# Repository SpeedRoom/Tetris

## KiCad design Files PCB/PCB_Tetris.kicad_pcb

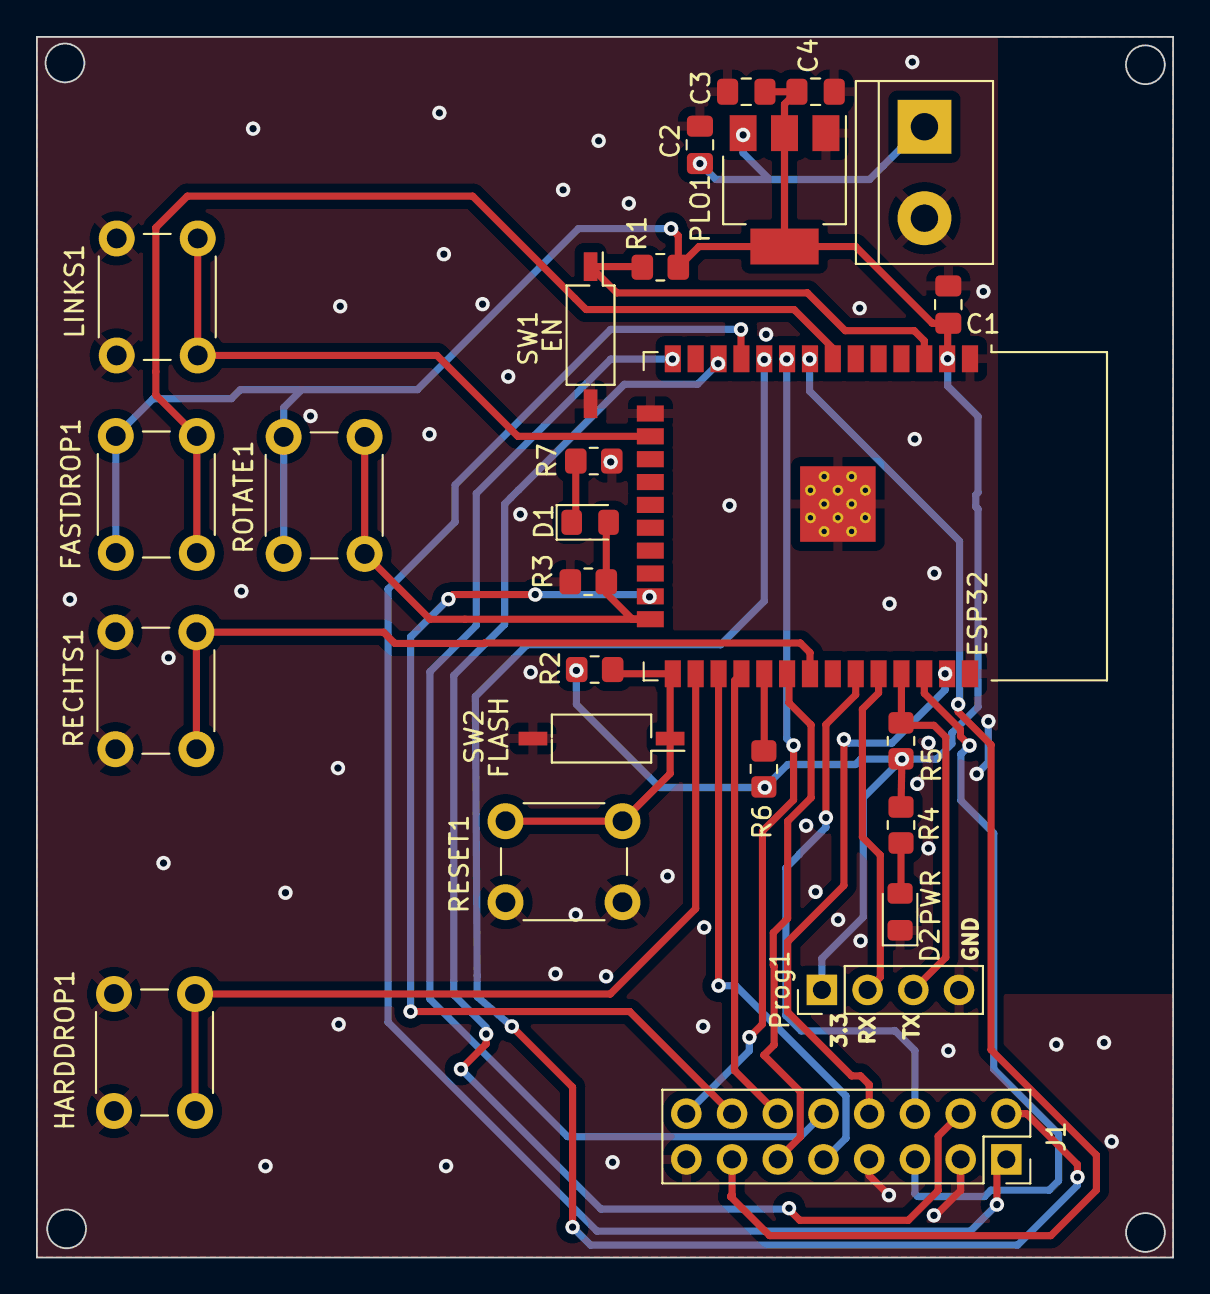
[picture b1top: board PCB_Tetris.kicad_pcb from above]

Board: 2 copper layers, 63.1 x 67.8 mm, 26 parts (0 on the bottom side), 28 nets.

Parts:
C1: 100uF/6.3V; C_0805_2012Metric_Pad1.18x1.45mm_HandSolder
C2, C4: 10uF; C_0805_2012Metric_Pad1.18x1.45mm_HandSolder
C3: 100nF; C_0805_2012Metric_Pad1.18x1.45mm_HandSolder
D1: BLUE; LED_0805_2012Metric_Pad1.15x1.40mm_HandSolder
D2: PWR; LED_0805_2012Metric_Pad1.15x1.40mm_HandSolder
ESP32: ESP32-WROOM-32
FASTDROP1: SW_Push; SW_PUSH_6mm
HARDDROP1: SW_Push; SW_PUSH_6mm
J1: Conn_02x08_Top_Bottom; PinSocket_2x08_P2.54mm_Vertical
Kroonsteen1: Screw_Terminal_01x02; TerminalBlock_bornier-2_P5.08mm
LINKS1: SW_Push; SW_PUSH_6mm
PLO1: AMS1117-3.3; SOT-223-3_TabPin2
Prog1: Conn_01x04_Pin; PinHeader_1x04_P2.54mm_Vertical
R1, R2, R3, R5, R6: 10K; R_0805_2012Metric_Pad1.20x1.40mm_HandSolder
R4, R7: 1K; R_0805_2012Metric_Pad1.20x1.40mm_HandSolder
RECHTS1: SW_Push; SW_PUSH_6mm
RESET1: SW_Push; SW_PUSH_6mm
ROTATE1: SW_Push; SW_PUSH_6mm
SW1: EN; SW_DIP_SPSTx01_Slide_Copal_CHS-01B_W7.62mm_P1.27mm
SW2: FLASH; SW_DIP_SPSTx01_Slide_Copal_CHS-01B_W7.62mm_P1.27mm

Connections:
+3.3V: C1.1, C3.2, C4.1, ESP32.2 (VDD), FASTDROP1.1, PLO1.2 (VO), Prog1.1, R1.1, R2.1, R4.1, R5.1, R6.1, ROTATE1.1
/EN: ESP32.3 (EN), R1.2, SW1.1
GND: C1.2, C2.2, C3.1, C4.2, D2.1 (K), ESP32.1 (GND), ESP32.15 (GND), ESP32.38 (GND), ESP32.39 (GND), HARDDROP1.1, J1.3, J1.7, J1.15, Kroonsteen1.2, LINKS1.1, PLO1.1 (GND), Prog1.4, R3.1, R7.2, RECHTS1.1, RESET1.1, SW1.2, SW2.2
GPIO0: ESP32.25 (IO0), R2.2, RESET1.2, SW2.1
GPIO2: D1.2 (A), ESP32.24 (IO2), R3.2, ROTATE1.2
GPIO4: ESP32.26 (IO4), HARDDROP1.2
GPIO5: ESP32.29 (IO5), R6.2
GPIO12: ESP32.14 (IO12), J1.10
GPIO13: ESP32.16 (IO13), LINKS1.2
GPIO15: ESP32.23 (IO15), J1.14
GPIO16: ESP32.27 (IO16), J1.9
GPIO17: ESP32.28 (IO17), J1.12
GPIO18: ESP32.30 (IO18), J1.11
GPIO19: ESP32.31 (IO19), RECHTS1.2
GPIO21: ESP32.33 (IO21), J1.6
GPIO22: ESP32.36 (IO22), J1.5
GPIO23: ESP32.37 (IO23), J1.8
GPIO25: ESP32.10 (IO25), J1.2
GPIO26: ESP32.11 (IO26), J1.1
GPIO27: ESP32.12 (IO27), J1.4
GPIO32: ESP32.8 (IO32), J1.13
GPIO33: ESP32.9 (IO33), J1.16
GPIO35: ESP32.7 (IO35), FASTDROP1.2
unnamed: D1.1 (K), R7.1
unnamed: D2.2 (A), R4.2
RX0: ESP32.34 (RXD0/IO3), Prog1.2
TX0: ESP32.35 (TXD0/IO1), Prog1.3, R5.2
VDD: C2.1, Kroonsteen1.1, PLO1.3 (VI)

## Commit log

2023-02-23 tetris
    Tetris op groot scherm, maar met grote fouten
2023-02-23 TETRIS WERKT!!!
    wel nog ma 2 knoppen ingesteld. unsigned long long is te klein!, andere oplossing gezocht.
2023-02-28 update met buttons
2023-02-28 update main
2023-02-28 opschoning txt
2023-03-02 update main
    normaal gezien dissplay_naam gefixt
2023-03-03 mats update
2023-03-06 Game over en herstart knop
2023-03-07 final version zonder cleaning
2023-03-07 geteste versie
2023-03-28 OTA added
2023-03-28 OTA updated
2023-04-29 MQTT toegevoegd
2023-04-29 mqtt update
2023-05-11 add code with extra classes
2023-05-11 update score = 0
2023-05-13 behuizing
2023-05-13 update start_game
2023-05-14 BOM_tetris
